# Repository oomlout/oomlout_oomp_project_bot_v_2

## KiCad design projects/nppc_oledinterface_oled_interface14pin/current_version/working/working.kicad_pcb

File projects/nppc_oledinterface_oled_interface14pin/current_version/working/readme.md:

# oledinterface
 
## summary 
* id: nppc_oledinterface_oled_interface14pin
* user: nppc
* name: oledinterface
* board: oled_interface14pin
* repo: https://github.com/nppc/OLEDInterface
* src_file_repo_kicad_pcb: OLED_Interface14pin.kicad_pcb
* src_file_repo_kicad_pcb_link: https://github.com/nppc/OLEDInterface/tree/master/OLED_Interface14pin.kicad_pcb

* src_file_repo_sch: OLED_Interface14pin.sch
* src_file_repo_sch_link: https://github.com/nppc/OLEDInterface/tree/master/OLED_Interface14pin.sch
* full details link: https://github.com/oomlout/oomlout_oomp_project_bot_v_2/tree/main/projects/nppc_oledinterface_oled_interface14pin/current_version/working

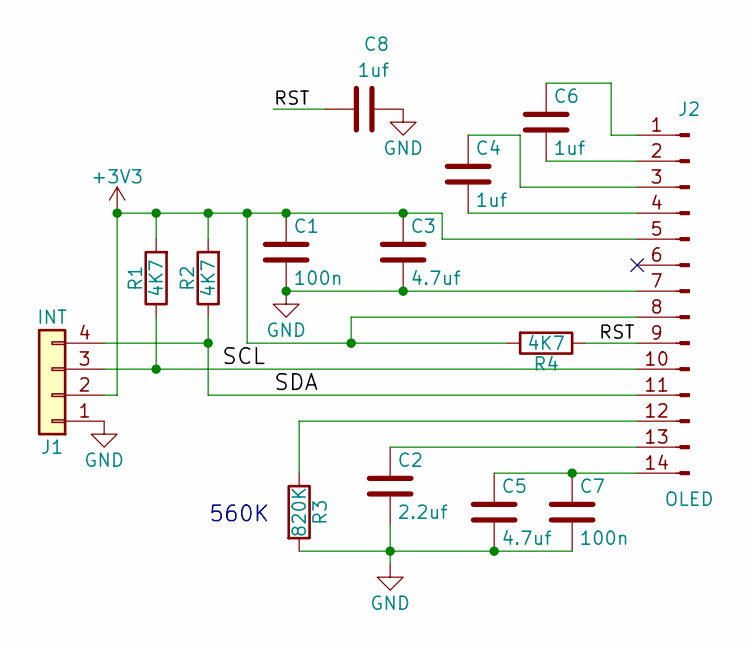
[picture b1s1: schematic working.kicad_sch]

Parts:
C1, C7: 100n; C_0402_NoSilk
C2: 2.2uf; C_0402_NoSilk
C3, C5: 4.7uf; C_0402_NoSilk
C4, C6, C8: 1uf; C_0402_NoSilk
J1: INT; SolderWirePad_4xInline_1-5mmDrill
J2: OLED; OLED_14pin
R1, R2, R4: 4K7; R_0402_NoSilk
R3: 820K; R_0402_NoSilk

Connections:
+3V3: C1.1, C3.1, J1.2, J2.5, J2.8, R1.2, R2.2, R4.2
/RST: C8.1, J2.9, R4.1
/SCL: J1.3, J2.10, R1.1
/SDA: J1.4, J2.11, R2.1
GND: C1.2, C2.2, C3.2, C5.2, C7.2, C8.2, J1.1, J2.7, R3.2
unnamed: C2.1, J2.13
unnamed: C4.1, J2.3
unnamed: C4.2, J2.4
unnamed: C5.1, C7.1, J2.14
unnamed: C6.1, J2.1
unnamed: C6.2, J2.2
unnamed: J2.12, R3.1

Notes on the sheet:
560K

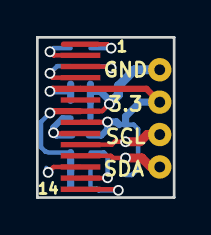
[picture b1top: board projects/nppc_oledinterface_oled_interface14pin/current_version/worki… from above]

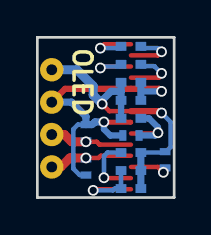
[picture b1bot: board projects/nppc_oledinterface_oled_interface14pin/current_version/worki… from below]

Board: 2 copper layers, 7.6 x 8.9 mm, 14 parts (12 on the bottom side), 12 nets.

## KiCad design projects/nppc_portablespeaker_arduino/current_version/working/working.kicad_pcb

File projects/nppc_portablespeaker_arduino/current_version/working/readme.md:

# portablespeaker
 
## summary 
* id: nppc_portablespeaker_arduino
* user: nppc
* name: portablespeaker
* board: arduino
* repo: https://github.com/nppc/PortableSpeaker
* src_file_repo_kicad_pcb: KiCad/Arduino/Arduino.kicad_pcb
* src_file_repo_kicad_pcb_link: https://github.com/nppc/PortableSpeaker/tree/master/KiCad/Arduino/Arduino.kicad_pcb

* src_file_repo_sch: KiCad/Arduino/Arduino.sch
* src_file_repo_sch_link: https://github.com/nppc/PortableSpeaker/tree/master/KiCad/Arduino/Arduino.sch
* full details link: https://github.com/oomlout/oomlout_oomp_project_bot_v_2/tree/main/projects/nppc_portablespeaker_arduino/current_version/working

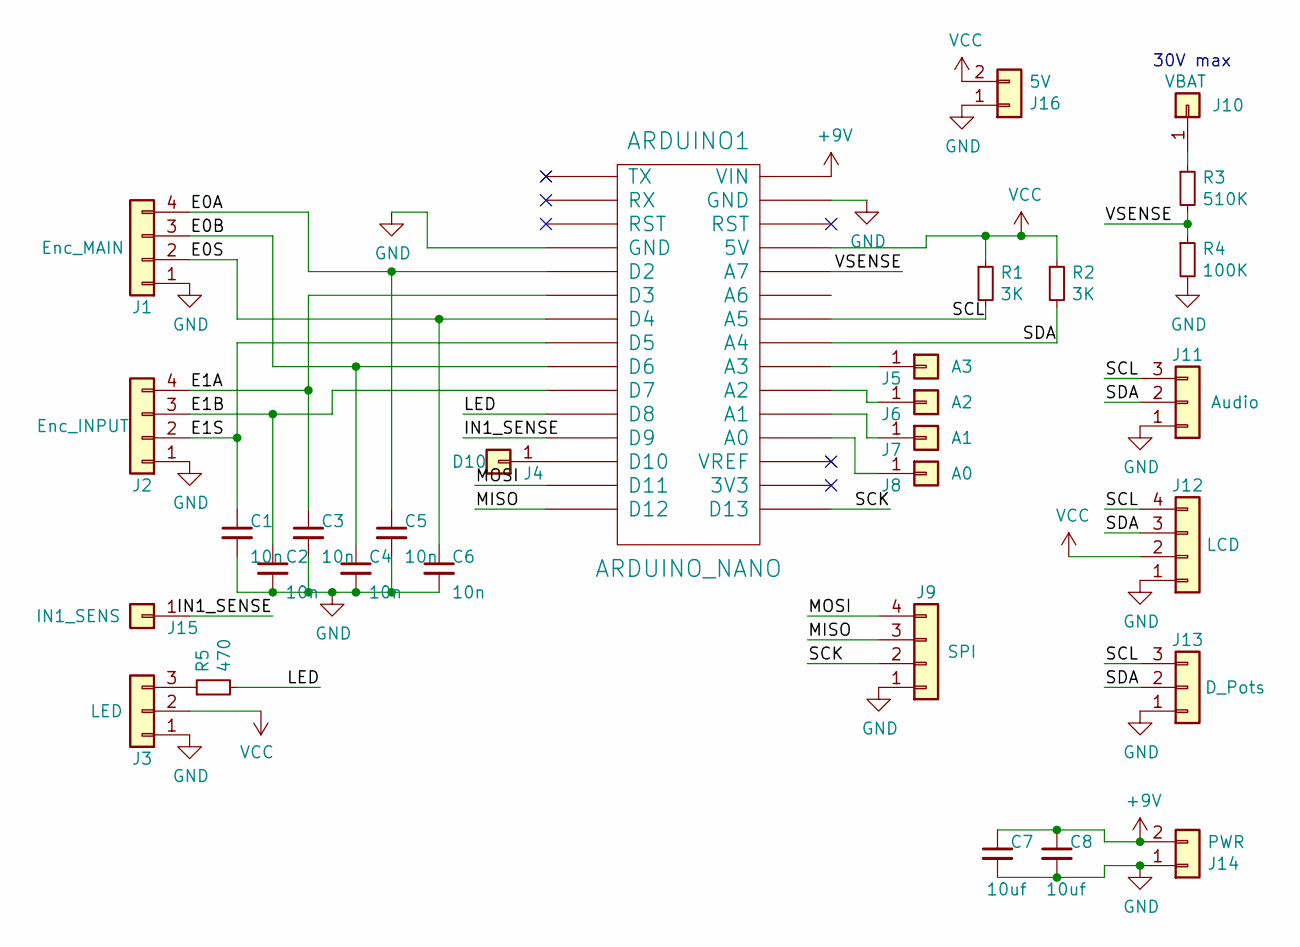
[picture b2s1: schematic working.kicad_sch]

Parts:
ARDUINO1: ARDUINO_NANO; arduino_nano
C1, C2, C3, C4, C5, C6: 10n; C_0603
C7, C8: 10uf; C_0603
J1: Enc_MAIN; Conn_1x04_2.54mm
J2: Enc_INPUT; Conn_1x04_2.54mm
J3: LED; Conn_1x03_2.54mm
J4: D10; Conn_1x01_2.54mm
J5: A3; Conn_1x01_2.54mm
J6: A2; Conn_1x01_2.54mm
J7: A1; Conn_1x01_2.54mm
J8: A0; Conn_1x01_2.54mm
J9: SPI; Conn_1x04_2.54mm
J10: VBAT; Conn_1x01_2.54mm
J11: Audio; Conn_1x03_2.54mm
J12: LCD; Conn_1x04_2.54mm
J13: D_Pots; Conn_1x03_2.54mm
J14: PWR; Conn_1x02_2.54mm
J15: IN1_SENS; Conn_1x01_2.54mm
J16: 5V; Conn_1x02_2.54mm
R1, R2: 3K; R_0603
R3: 510K; R_0603
R4: 100K; R_0603
R5: 470; R_0603

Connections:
+9V: ARDUINO1.30 (VIN), C7.1, C8.1, J14.2
/E0A: ARDUINO1.5 (D2), C5.1, J1.4
/E0B: ARDUINO1.9 (D6), C4.1, J1.3
/E0C: ARDUINO1.7 (D4), C6.1, J1.2
/E1A: ARDUINO1.6 (D3), C3.1, J2.4
/E1B: ARDUINO1.10 (D7), C2.1, J2.3
/E1C: ARDUINO1.8 (D5), C1.1, J2.2
/IN1_SENSE: ARDUINO1.12 (D9), J15.1
/LED: ARDUINO1.11 (D8), R5.2
/MISO: ARDUINO1.15 (D12), J9.3
/MOSI: ARDUINO1.14 (D11), J9.4
/SCK: ARDUINO1.16 (D13), J9.2
/SCL: ARDUINO1.24 (A5), J11.3, J12.4, J13.3, R1.2
/SDA: ARDUINO1.23 (A4), J11.2, J12.3, J13.2, R2.2
/VSENSE: ARDUINO1.26 (A7), R3.2, R4.1
GND: ARDUINO1.4 (GND), ARDUINO1.29 (GND), C1.2, C2.2, C3.2, C4.2, C5.2, C6.2, C7.2, C8.2, J1.1, J2.1, J3.1, J9.1, J11.1, J12.1, J13.1, J14.1, J16.1, R4.2
unnamed: ARDUINO1.13 (D10), J4.1
unnamed: ARDUINO1.19 (A0), J8.1
unnamed: ARDUINO1.20 (A1), J7.1
unnamed: ARDUINO1.21 (A2), J6.1
unnamed: ARDUINO1.22 (A3), J5.1
unnamed: J3.3, R5.1
unnamed: J10.1, R3.1
VCC: ARDUINO1.27 (5V), J3.2, J12.2, J16.2, R1.1, R2.1

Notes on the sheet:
30V max

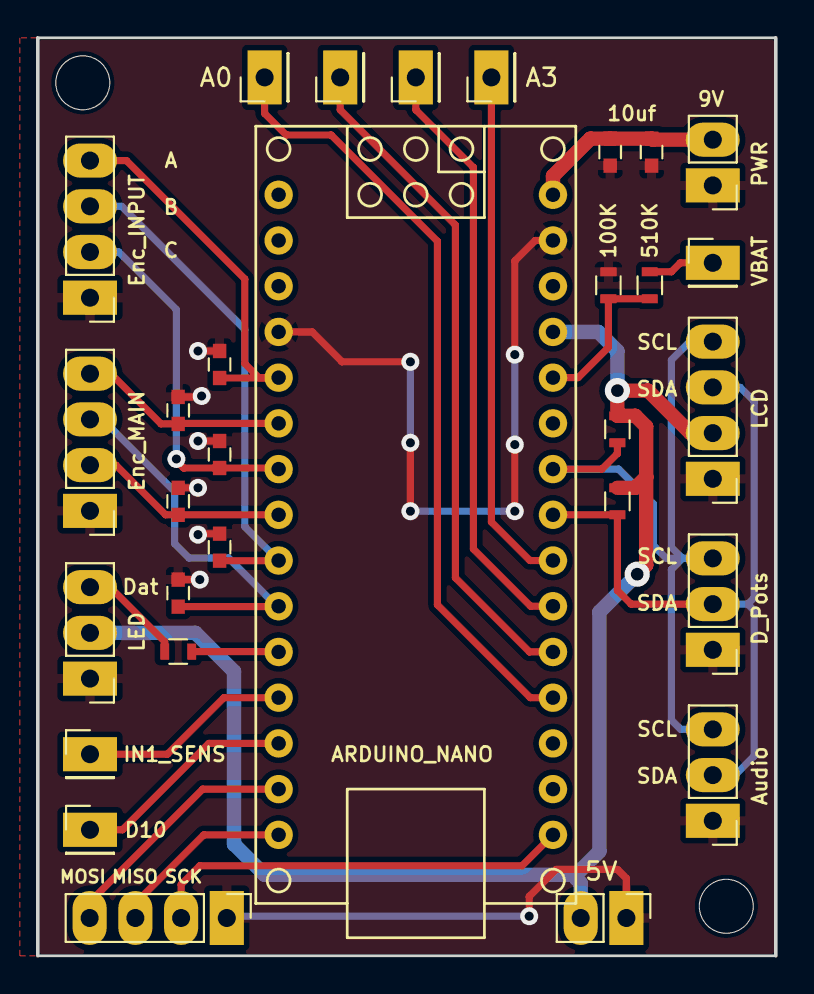
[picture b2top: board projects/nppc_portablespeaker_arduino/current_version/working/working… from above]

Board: 2 copper layers, 41.0 x 51.0 mm, 30 parts (0 on the bottom side), 24 nets.

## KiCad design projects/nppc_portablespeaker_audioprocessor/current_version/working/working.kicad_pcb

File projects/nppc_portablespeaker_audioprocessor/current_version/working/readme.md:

# portablespeaker
 
## summary 
* id: nppc_portablespeaker_audioprocessor
* user: nppc
* name: portablespeaker
* board: audioprocessor
* repo: https://github.com/nppc/PortableSpeaker
* src_file_repo_kicad_pcb: KiCad/AudioProcessor/AudioProcessor.kicad_pcb
* src_file_repo_kicad_pcb_link: https://github.com/nppc/PortableSpeaker/tree/master/KiCad/AudioProcessor/AudioProcessor.kicad_pcb

* src_file_repo_sch: KiCad/AudioProcessor/AudioProcessor.sch
* src_file_repo_sch_link: https://github.com/nppc/PortableSpeaker/tree/master/KiCad/AudioProcessor/AudioProcessor.sch
* full details link: https://github.com/oomlout/oomlout_oomp_project_bot_v_2/tree/main/projects/nppc_portablespeaker_audioprocessor/current_version/working

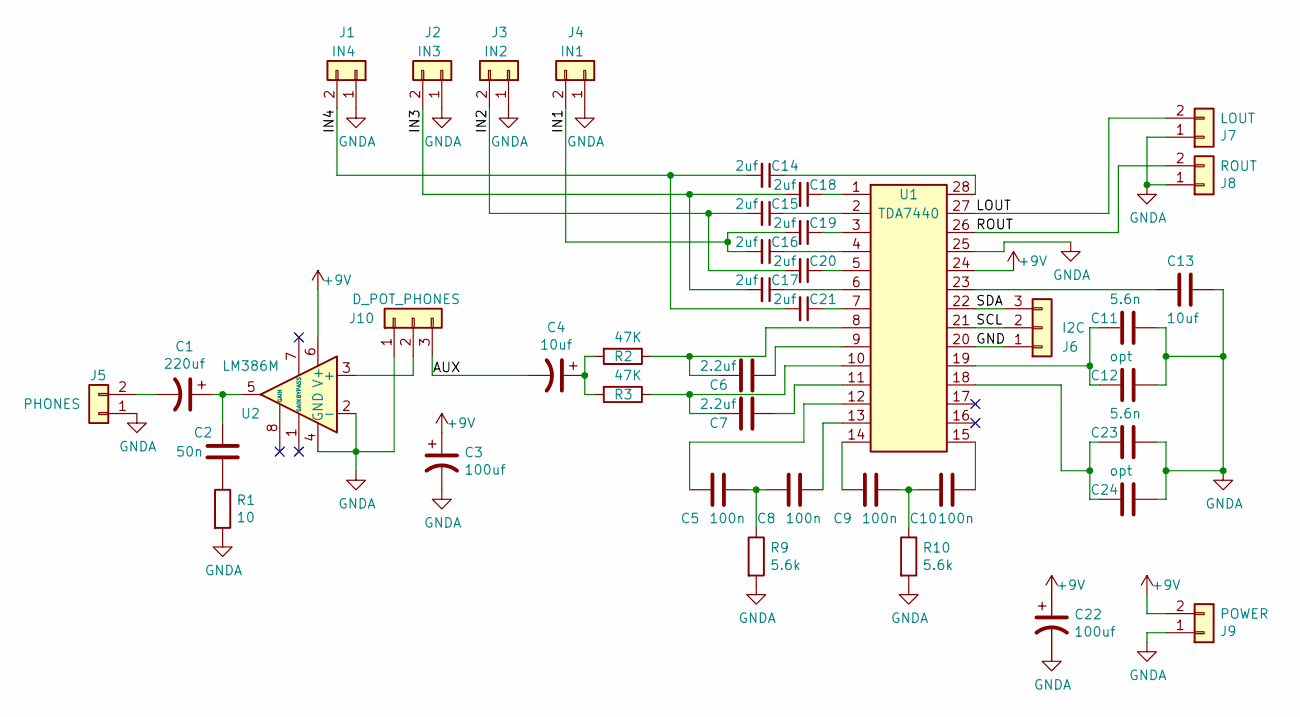
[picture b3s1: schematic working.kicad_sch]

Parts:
C1: 220uf; CP_Radial_Tantal_D8.0mm_P5.00mm
C2: 50n; C_0603
C3, C22: 100uf; CP_Radial_Tantal_D6.0mm_P5.00mm
C4: 10uf; CP_Radial_Tantal_D4.5mm_P2.50mm
C5, C8, C9, C10: 100n; C_Rect_L7.2mm_W2.5mm_P5.00mm_FKS2_FKP2_MKS2_MKP2
C6, C7: 2.2uf; C_0603
C11, C23: 5.6n; C_0805
C12, C24: opt; C_0805
C13: 10uf; C_0603
C14, C15, C16, C17, C18, C19, C20, C21: 2uf; C_0603
J1: IN4; Conn_1x02_2.54mm
J2: IN3; Conn_1x02_2.54mm
J3: IN2; Conn_1x02_2.54mm
J4: IN1; Conn_1x02_2.54mm
J5: PHONES; Conn_1x02_2.54mm
J6: I2C; Conn_1x03_2.54mm
J7: LOUT; Conn_1x02_2.54mm
J8: ROUT; Conn_1x02_2.54mm
J9: POWER; Conn_1x02_2.54mm
J10: D_POT_PHONES; Conn_1x03_2.54mm
R1: 10; R_0603
R2, R3: 47K; R_0603
R9, R10: 5.6k; R_0603
U1: TDA7440; SOIC-28W_7.5x17.9mm_Pitch1.27mm
U2: LM386M; DIP-8_W7.62mm_Socket

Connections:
+9V: C3.1, C22.1, J9.2, U1.24, U2.6 (V+)
/AUX: C4.2, J10.3
/GND: J6.1, U1.20
/IN1: C16.2, C19.2, J4.2
/IN2: C15.2, C20.2, J3.2
/IN3: C17.2, C18.2, J2.2
/IN4: C14.2, C21.2, J1.2
/LOUT: J7.2, U1.27
/ROUT: J8.2, U1.26
/SCL: J6.2, U1.21
/SDA: J6.3, U1.22
GNDA: C3.2, C11.1, C12.1, C13.1, C22.2, C23.1, C24.1, J1.1, J2.1, J3.1, J4.1, J5.1, J7.1, J8.1, J9.1, J10.1, R1.2, R9.2, R10.2, U1.25, U2.2 (-), U2.4 (GND)
unnamed: C1.1, C2.2, U2.5
unnamed: C1.2, J5.2
unnamed: C2.1, R1.1
unnamed: C4.1, R2.2, R3.2
unnamed: C5.1, C8.2, R9.1
unnamed: C5.2, U1.12
unnamed: C6.1, U1.9
unnamed: C6.2, R2.1, U1.8
unnamed: C7.1, U1.11
unnamed: C7.2, R3.1, U1.10
unnamed: C8.1, U1.13
unnamed: C9.2, U1.14
unnamed: C10.1, U1.15
unnamed: C9.1, C10.2, R10.1
unnamed: C11.2, C12.2, U1.19
unnamed: C13.2, U1.23
unnamed: C14.1, U1.28
unnamed: C15.1, U1.2
unnamed: C16.1, U1.4
unnamed: C17.1, U1.6
unnamed: C18.1, U1.1
unnamed: C19.1, U1.3
unnamed: C20.1, U1.5
unnamed: C21.1, U1.7
unnamed: C23.2, C24.2, U1.18
unnamed: J10.2, U2.3 (+)

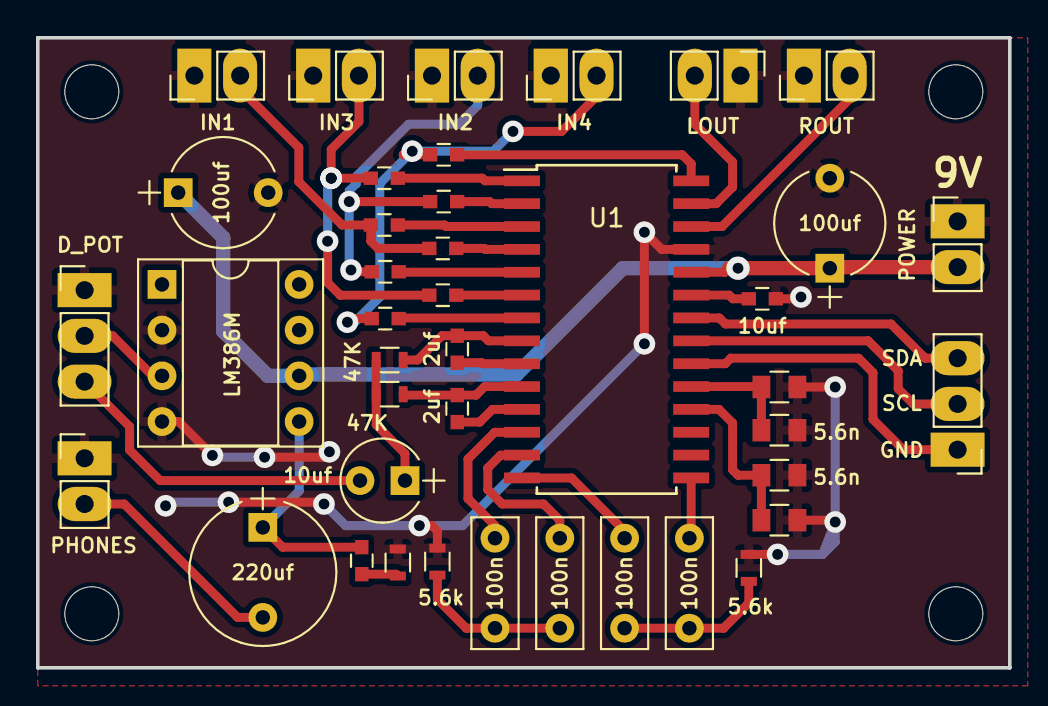
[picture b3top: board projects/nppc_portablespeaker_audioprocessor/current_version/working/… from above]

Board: 2 copper layers, 54.0 x 35.0 mm, 41 parts (0 on the bottom side), 38 nets.

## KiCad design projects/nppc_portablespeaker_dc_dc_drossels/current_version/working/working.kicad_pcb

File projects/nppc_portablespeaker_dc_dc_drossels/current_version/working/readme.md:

# portablespeaker
 
## summary 
* id: nppc_portablespeaker_dc_dc_drossels
* user: nppc
* name: portablespeaker
* board: dc_dc_drossels
* repo: https://github.com/nppc/PortableSpeaker
* src_file_repo_kicad_pcb: KiCad/DC-DC-Drossels/DC-DC-Drossels.kicad_pcb
* src_file_repo_kicad_pcb_link: https://github.com/nppc/PortableSpeaker/tree/master/KiCad/DC-DC-Drossels/DC-DC-Drossels.kicad_pcb

* src_file_repo_sch: KiCad/DC-DC-Drossels/DC-DC-Drossels.sch
* src_file_repo_sch_link: https://github.com/nppc/PortableSpeaker/tree/master/KiCad/DC-DC-Drossels/DC-DC-Drossels.sch
* full details link: https://github.com/oomlout/oomlout_oomp_project_bot_v_2/tree/main/projects/nppc_portablespeaker_dc_dc_drossels/current_version/working

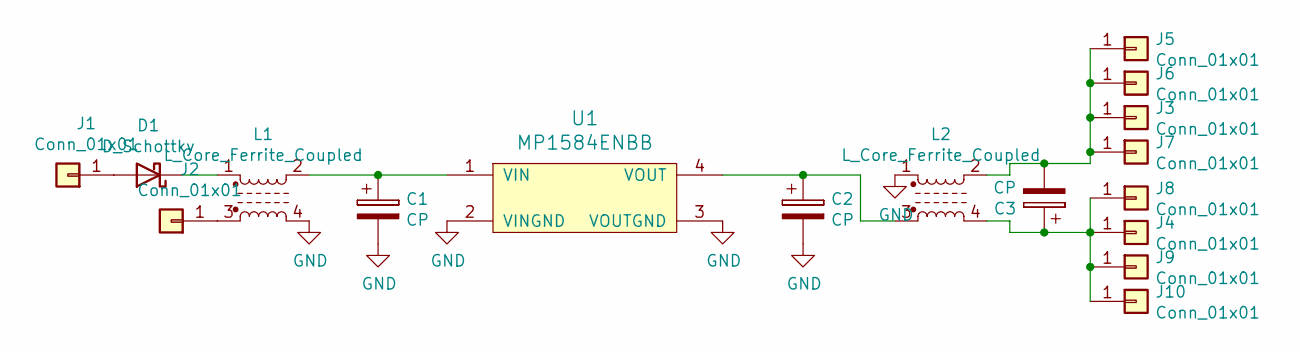
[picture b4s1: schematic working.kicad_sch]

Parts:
C1, C2: CP; CP_Radial_D8.0mm_P3.50mm
C3: CP; CP_Radial_D13.0mm_P5.00mm
D1: D_Schottky; D_DO-15_P10.16mm_Horizontal
J1, J2, J3, J4, J5, J6, J7, J8, J9, J10: Conn_01x01; SolderWirePad_single_2mmDrill
L1, L2: L_Core_Ferrite_Coupled; L_CommonMode_Wuerth_WE-CMB-XS
U1: MP1584ENBB; DIP-4_W7.62mm

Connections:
GND: C1.2, C2.2, L1.4, L2.1, U1.2 (VINGND), U1.3 (VOUTGND)
unnamed: C1.1, L1.2, U1.1 (VIN)
unnamed: C2.1, L2.3, U1.4 (VOUT)
unnamed: C3.1, J4.1, J8.1, J9.1, J10.1, L2.4
unnamed: C3.2, J3.1, J5.1, J6.1, J7.1, L2.2
unnamed: D1.1 (K), L1.1
unnamed: D1.2 (A), J1.1
unnamed: J2.1, L1.3

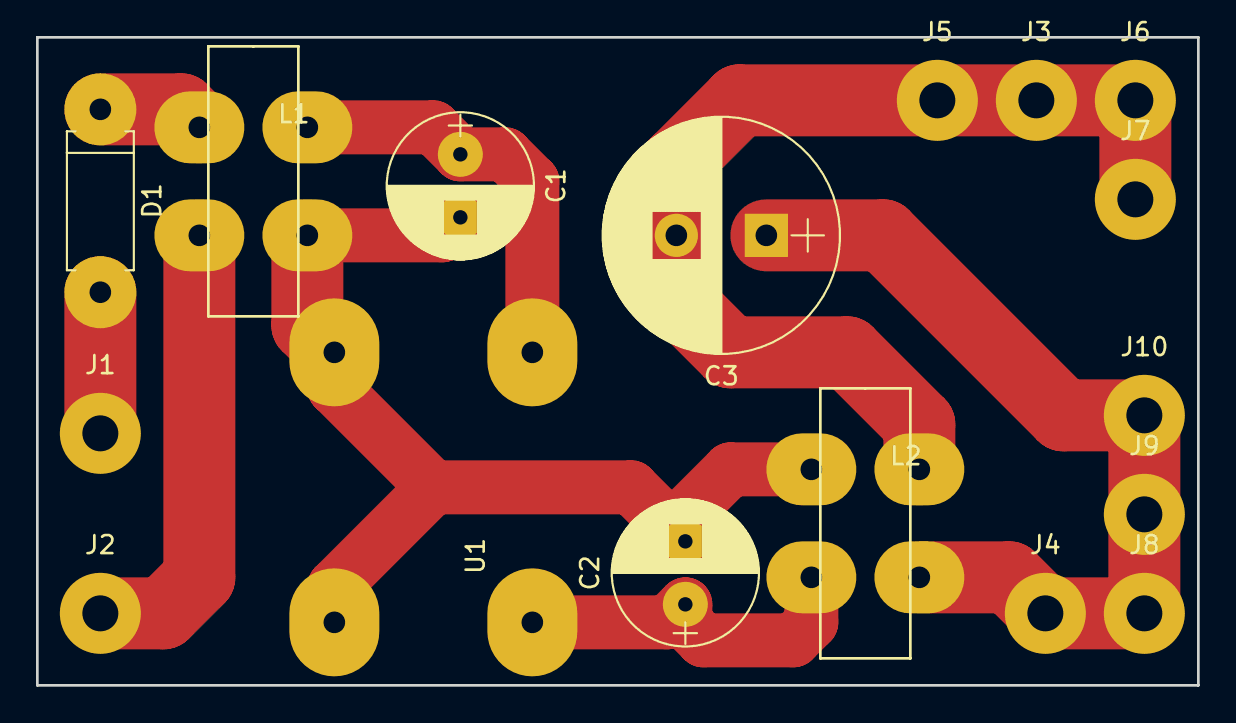
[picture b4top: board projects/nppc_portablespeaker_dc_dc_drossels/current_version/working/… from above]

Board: 2 copper layers, 64.5 x 36.0 mm, 17 parts (0 on the bottom side), 8 nets.

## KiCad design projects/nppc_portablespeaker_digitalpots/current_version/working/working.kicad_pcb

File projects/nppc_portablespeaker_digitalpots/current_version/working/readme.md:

# portablespeaker
 
## summary 
* id: nppc_portablespeaker_digitalpots
* user: nppc
* name: portablespeaker
* board: digitalpots
* repo: https://github.com/nppc/PortableSpeaker
* src_file_repo_kicad_pcb: KiCad/DigitalPots/DigitalPots.kicad_pcb
* src_file_repo_kicad_pcb_link: https://github.com/nppc/PortableSpeaker/tree/master/KiCad/DigitalPots/DigitalPots.kicad_pcb

* src_file_repo_sch: KiCad/DigitalPots/DigitalPots.sch
* src_file_repo_sch_link: https://github.com/nppc/PortableSpeaker/tree/master/KiCad/DigitalPots/DigitalPots.sch
* full details link: https://github.com/oomlout/oomlout_oomp_project_bot_v_2/tree/main/projects/nppc_portablespeaker_digitalpots/current_version/working

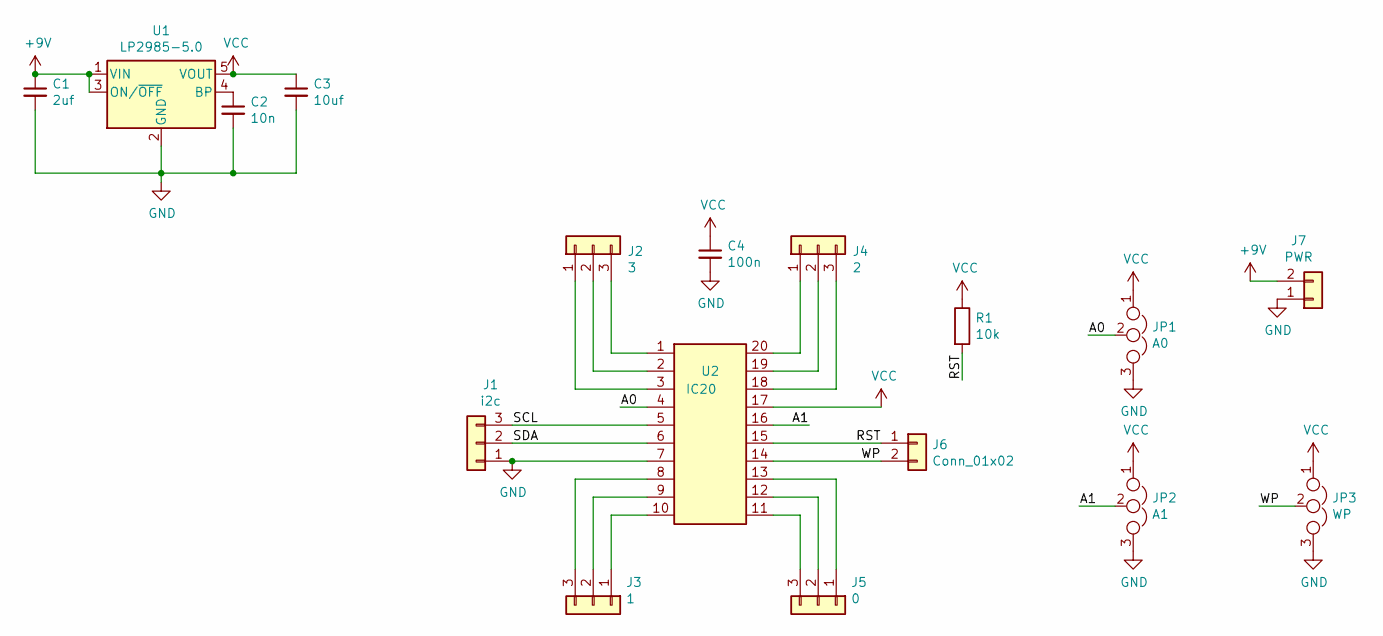
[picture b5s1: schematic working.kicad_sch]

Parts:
C1: 2uf; C_0603
C2: 10n; C_0603
C3: 10uf; C_0603
C4: 100n; C_0603
J1: i2c; Conn_1x03_2.54mm
J2: 3; Conn_1x03_2.54mm
J3: 1; Conn_1x03_2.54mm
J4: 2; Conn_1x03_2.54mm
J5: 0; Conn_1x03_2.54mm
J6: Conn_01x02; Conn_1x02_2.54mm
J7: PWR; Conn_1x02_2.54mm
JP1: A0; SolderJumper-3_P1.3mm_Open_Pad1.0x1.5mm_NumberLabels
JP2: A1; SolderJumper-3_P1.3mm_Open_Pad1.0x1.5mm_NumberLabels
JP3: WP; SolderJumper-3_P1.3mm_Open_Pad1.0x1.5mm_NumberLabels
R1: 10k; R_0603
U1: LP2985-5.0; SOT-23-5
U2: IC20; TSSOP-20_4.4x6.5mm_Pitch0.65mm

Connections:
+9V: C1.1, J7.2, U1.1 (VIN), U1.3 (ON/~OFF)
/A0: JP1.2, U2.4
/A1: JP2.2, U2.16
/RST: J6.1, R1.2, U2.15
/SCL: J1.3, U2.5
/SDA: J1.2, U2.6
/WP: J6.2, JP3.2, U2.14
GND: C1.2, C2.2, C3.2, C4.2, J1.1, J7.1, JP1.3, JP2.3, JP3.3, U1.2 (GND), U2.7
unnamed: C2.1, U1.4 (BP)
unnamed: J2.1, U2.3
unnamed: J2.2, U2.2
unnamed: J2.3, U2.1
unnamed: J3.1, U2.10
unnamed: J3.2, U2.9
unnamed: J3.3, U2.8
unnamed: J4.1, U2.20
unnamed: J4.2, U2.19
unnamed: J4.3, U2.18
unnamed: J5.1, U2.13
unnamed: J5.2, U2.12
unnamed: J5.3, U2.11
VCC: C3.1, C4.1, JP1.1, JP2.1, JP3.1, R1.1, U1.5 (VOUT), U2.17

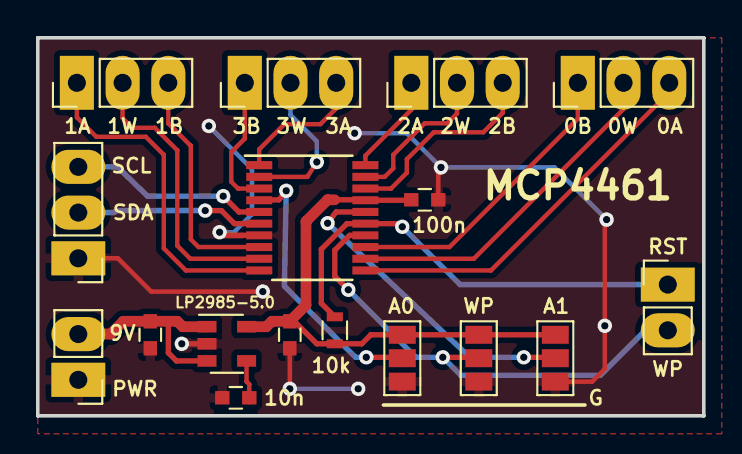
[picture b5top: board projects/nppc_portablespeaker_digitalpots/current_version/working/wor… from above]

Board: 2 copper layers, 37.0 x 21.0 mm, 17 parts (0 on the bottom side), 22 nets.

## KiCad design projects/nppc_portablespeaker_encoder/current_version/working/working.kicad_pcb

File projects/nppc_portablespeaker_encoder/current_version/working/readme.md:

# portablespeaker
 
## summary 
* id: nppc_portablespeaker_encoder
* user: nppc
* name: portablespeaker
* board: encoder
* repo: https://github.com/nppc/PortableSpeaker
* src_file_repo_kicad_pcb: KiCad/Encoder/Encoder.kicad_pcb
* src_file_repo_kicad_pcb_link: https://github.com/nppc/PortableSpeaker/tree/master/KiCad/Encoder/Encoder.kicad_pcb

* src_file_repo_sch: KiCad/Encoder/Encoder.sch
* src_file_repo_sch_link: https://github.com/nppc/PortableSpeaker/tree/master/KiCad/Encoder/Encoder.sch
* full details link: https://github.com/oomlout/oomlout_oomp_project_bot_v_2/tree/main/projects/nppc_portablespeaker_encoder/current_version/working

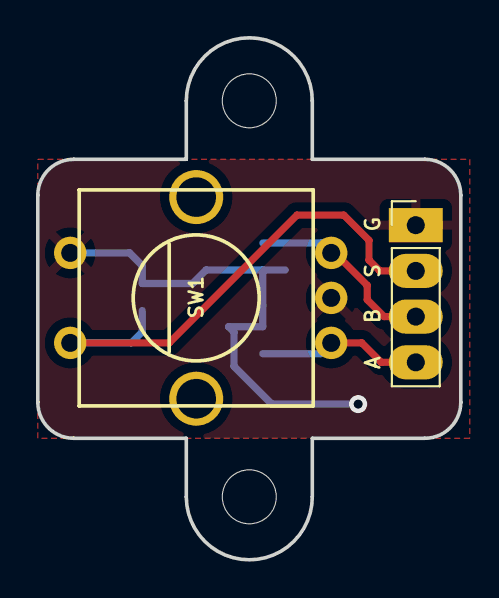
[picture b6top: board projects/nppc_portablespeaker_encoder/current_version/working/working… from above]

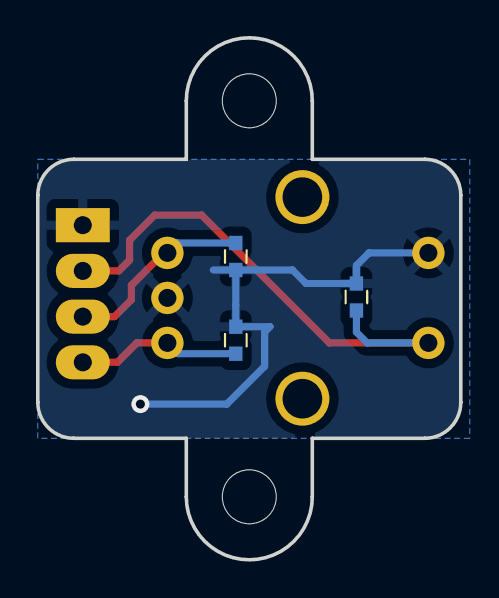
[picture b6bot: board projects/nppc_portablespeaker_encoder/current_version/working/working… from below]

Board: 2 copper layers, 23.5 x 29.0 mm, 5 parts (3 on the bottom side), 4 nets.

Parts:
C1, C2, C3: C_Small; C_0603
J1: Conn_01x04; Conn_1x04_2.54mm
SW1: Rotary_Encoder_Switch; ROTARY-ENCODER

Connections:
GND: C1.2, C2.2, C3.2, J1.1, SW1.2, SW1.5
unnamed: C1.1, J1.2, SW1.4
unnamed: C2.1, J1.4, SW1.1
unnamed: C3.1, J1.3, SW1.3
